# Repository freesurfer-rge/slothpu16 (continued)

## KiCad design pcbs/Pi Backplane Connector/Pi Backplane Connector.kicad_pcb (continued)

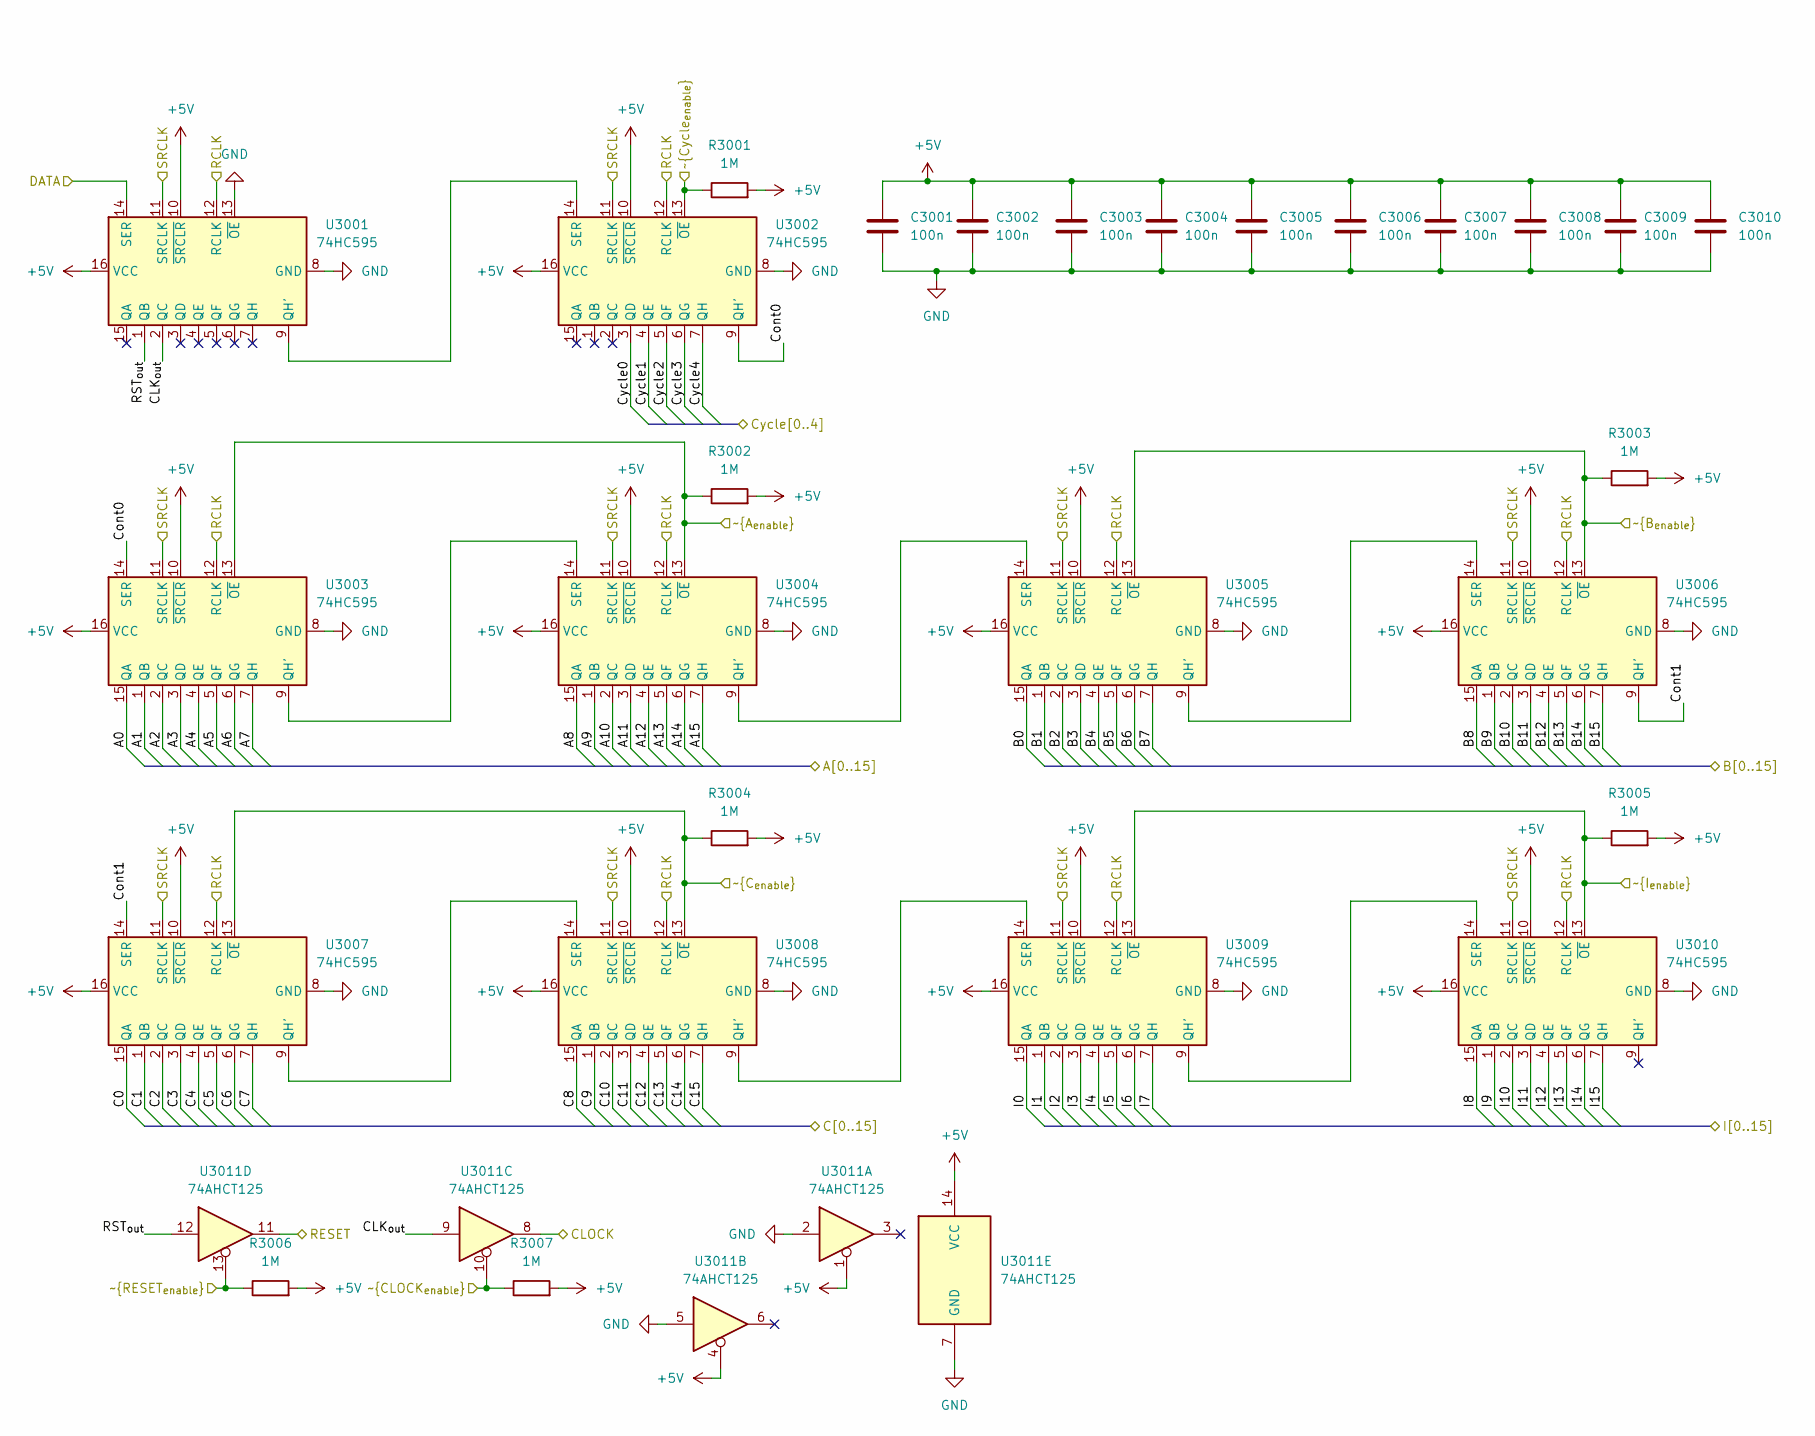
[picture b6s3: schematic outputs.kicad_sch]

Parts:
C3001, C3002, C3003, C3004, C3005, C3006, C3007, C3008, C3009, C3010: 100n; C_0603_1608Metric; LCSC C14663
R3001, R3002, R3003, R3004, R3005, R3006, R3007: 1M; R_0603_1608Metric; LCSC C22935
U3001, U3002, U3003, U3004, U3005, U3006, U3007, U3008, U3009, U3010: 74HC595; SO-16_3.9x9.9mm_P1.27mm; LCSC C5947
U3011: 74AHCT125; DIP-14_W7.62mm_Socket

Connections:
+5V: C3001.2, C3002.2, C3003.2, C3004.2, C3005.2, C3006.2, C3007.2, C3008.2, C3009.2, C3010.2, R3001.2, R3002.2, R3003.2, R3004.2, R3005.2, R3006.2, R3007.2, U3001.10 (~SRCLR), U3001.16 (VCC), U3002.10 (~SRCLR), U3002.16 (VCC), U3003.10 (~SRCLR), U3003.16 (VCC), U3004.10 (~SRCLR), U3004.16 (VCC), U3005.10 (~SRCLR), U3005.16 (VCC), U3006.10 (~SRCLR), U3006.16 (VCC), U3007.10 (~SRCLR), U3007.16 (VCC), U3008.10 (~SRCLR), U3008.16 (VCC), U3009.10 (~SRCLR), U3009.16 (VCC), U3010.10 (~SRCLR), U3010.16 (VCC), U3011.1, U3011.4, U3011.14 (VCC); also elsewhere on the board
/A0: U3003.15 (QA); also elsewhere on the board
/A1: U3003.1 (QB); also elsewhere on the board
/A2: U3003.2 (QC); also elsewhere on the board
/A3: U3003.3 (QD); also elsewhere on the board
/A4: U3003.4 (QE); also elsewhere on the board
/A5: U3003.5 (QF); also elsewhere on the board
/A6: U3003.6 (QG); also elsewhere on the board
/A7: U3003.7 (QH); also elsewhere on the board
/A8: U3004.15 (QA); also elsewhere on the board
/A9: U3004.1 (QB); also elsewhere on the board
/A10: U3004.2 (QC); also elsewhere on the board
/A11: U3004.3 (QD); also elsewhere on the board
/A12: U3004.4 (QE); also elsewhere on the board
/A13: U3004.5 (QF); also elsewhere on the board
/A14: U3004.6 (QG); also elsewhere on the board
/A15: U3004.7 (QH); also elsewhere on the board
/B0: U3005.15 (QA); also elsewhere on the board
/B1: U3005.1 (QB); also elsewhere on the board
/B2: U3005.2 (QC); also elsewhere on the board
/B3: U3005.3 (QD); also elsewhere on the board
/B4: U3005.4 (QE); also elsewhere on the board
/B5: U3005.5 (QF); also elsewhere on the board
/B6: U3005.6 (QG); also elsewhere on the board
/B7: U3005.7 (QH); also elsewhere on the board
/B8: U3006.15 (QA); also elsewhere on the board
/B9: U3006.1 (QB); also elsewhere on the board
/B10: U3006.2 (QC); also elsewhere on the board
/B11: U3006.3 (QD); also elsewhere on the board
/B12: U3006.4 (QE); also elsewhere on the board
/B13: U3006.5 (QF); also elsewhere on the board
/B14: U3006.6 (QG); also elsewhere on the board
/B15: U3006.7 (QH); also elsewhere on the board
/C0: U3007.15 (QA); also elsewhere on the board
/C1: U3007.1 (QB); also elsewhere on the board
/C2: U3007.2 (QC); also elsewhere on the board
/C3: U3007.3 (QD); also elsewhere on the board
/C4: U3007.4 (QE); also elsewhere on the board
/C5: U3007.5 (QF); also elsewhere on the board
/C6: U3007.6 (QG); also elsewhere on the board
/C7: U3007.7 (QH); also elsewhere on the board
/C8: U3008.15 (QA); also elsewhere on the board
/C9: U3008.1 (QB); also elsewhere on the board
/C10: U3008.2 (QC); also elsewhere on the board
/C11: U3008.3 (QD); also elsewhere on the board
/C12: U3008.4 (QE); also elsewhere on the board
/C13: U3008.5 (QF); also elsewhere on the board
/C14: U3008.6 (QG); also elsewhere on the board
/C15: U3008.7 (QH); also elsewhere on the board
/CLOCK: U3011.8; also elsewhere on the board
/Cycle0: U3002.3 (QD); also elsewhere on the board
/Cycle1: U3002.4 (QE); also elsewhere on the board
/Cycle2: U3002.5 (QF); also elsewhere on the board
/Cycle3: U3002.6 (QG); also elsewhere on the board
/Cycle4: U3002.7 (QH); also elsewhere on the board
/I0: U3009.15 (QA); also elsewhere on the board
/I1: U3009.1 (QB); also elsewhere on the board
/I2: U3009.2 (QC); also elsewhere on the board
/I3: U3009.3 (QD); also elsewhere on the board
/I4: U3009.4 (QE); also elsewhere on the board
/I5: U3009.5 (QF); also elsewhere on the board
/I6: U3009.6 (QG); also elsewhere on the board
/I7: U3009.7 (QH); also elsewhere on the board
/I8: U3010.15 (QA); also elsewhere on the board
/I9: U3010.1 (QB); also elsewhere on the board
/I10: U3010.2 (QC); also elsewhere on the board
/I11: U3010.3 (QD); also elsewhere on the board
/I12: U3010.4 (QE); also elsewhere on the board
/I13: U3010.5 (QF); also elsewhere on the board
/I14: U3010.6 (QG); also elsewhere on the board
/I15: U3010.7 (QH); also elsewhere on the board
/Outputs/CLK_{out}: U3001.2 (QC), U3011.9
/Outputs/Cont0: U3002.9 (QH'), U3003.14 (SER)
/Outputs/Cont1: U3006.9 (QH'), U3007.14 (SER)
/Outputs/DATA: U3001.14 (SER); also elsewhere on the board
/Outputs/RCLK: U3001.12 (RCLK), U3002.12 (RCLK), U3003.12 (RCLK), U3004.12 (RCLK), U3005.12 (RCLK), U3006.12 (RCLK), U3007.12 (RCLK), U3008.12 (RCLK), U3009.12 (RCLK), U3010.12 (RCLK); also elsewhere on the board
/Outputs/RST_{out}: U3001.1 (QB), U3011.12
/Outputs/SRCLK: U3001.11 (SRCLK), U3002.11 (SRCLK), U3003.11 (SRCLK), U3004.11 (SRCLK), U3005.11 (SRCLK), U3006.11 (SRCLK), U3007.11 (SRCLK), U3008.11 (SRCLK), U3009.11 (SRCLK), U3010.11 (SRCLK); also elsewhere on the board
/Outputs/~A_{enable}: R3002.1, U3003.13 (~OE), U3004.13 (~OE); also elsewhere on the board
/Outputs/~B_{enable}: R3003.1, U3005.13 (~OE), U3006.13 (~OE); also elsewhere on the board
/Outputs/~CLOCK_{enable}: R3007.1, U3011.10; also elsewhere on the board
/Outputs/~C_{enable}: R3004.1, U3007.13 (~OE), U3008.13 (~OE); also elsewhere on the board
/Outputs/~Cycle_{enable}: R3001.1, U3002.13 (~OE); also elsewhere on the board
/Outputs/~I_{enable}: R3005.1, U3009.13 (~OE), U3010.13 (~OE); also elsewhere on the board
/Outputs/~RESET_{enable}: R3006.1, U3011.13; also elsewhere on the board
/RESET: U3011.11; also elsewhere on the board
GND: C3001.1, C3002.1, C3003.1, C3004.1, C3005.1, C3006.1, C3007.1, C3008.1, C3009.1, C3010.1, U3001.8 (GND), U3001.13 (~OE), U3002.8 (GND), U3003.8 (GND), U3004.8 (GND), U3005.8 (GND), U3006.8 (GND), U3007.8 (GND), U3008.8 (GND), U3009.8 (GND), U3010.8 (GND), U3011.2, U3011.5, U3011.7 (GND); also elsewhere on the board
unnamed: U3001.9 (QH'), U3002.14 (SER)
unnamed: U3003.9 (QH'), U3004.14 (SER)
unnamed: U3004.9 (QH'), U3005.14 (SER)
unnamed: U3005.9 (QH'), U3006.14 (SER)
unnamed: U3007.9 (QH'), U3008.14 (SER)
unnamed: U3008.9 (QH'), U3009.14 (SER)
unnamed: U3009.9 (QH'), U3010.14 (SER)

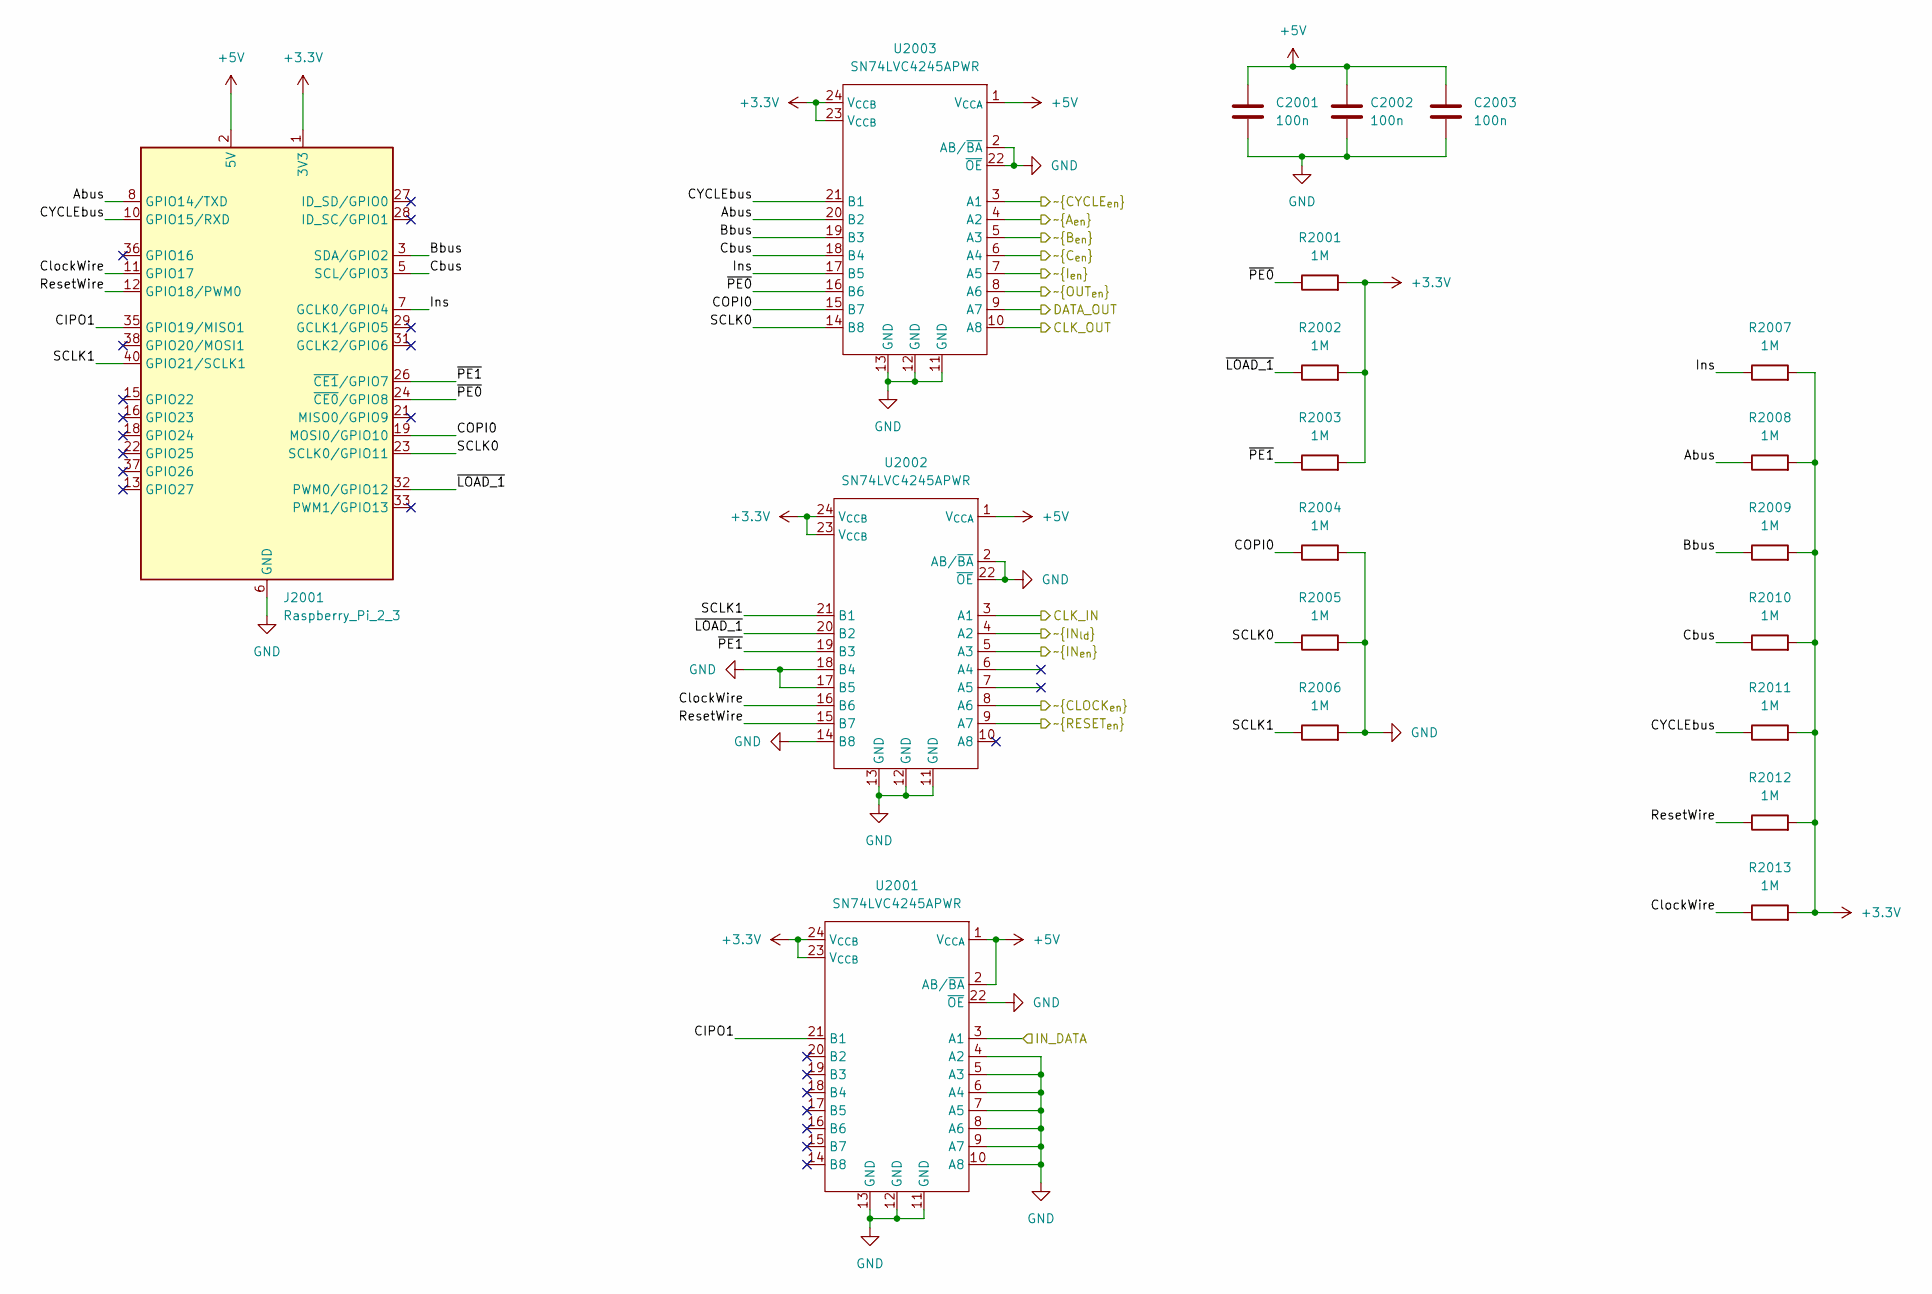
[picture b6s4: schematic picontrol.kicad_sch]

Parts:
C2001, C2002, C2003: 100n; C_0603_1608Metric; LCSC C14663
J2001: Raspberry_Pi_2_3; PinHeader_2x20_P2.54mm_Vertical
R2001, R2002, R2003, R2004, R2005, R2006, R2007, R2008, R2009, R2010, R2011, R2012, R2013: 1M; R_0603_1608Metric; LCSC C22935
U2001, U2002, U2003: SN74LVC4245APWR; TSSOP-24_4.4x7.8mm_P0.65mm; LCSC C7859

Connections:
+3.3V: J2001.1 (3V3), J2001.17 (3V3), R2001.2, R2002.2, R2003.2, R2007.2, R2008.2, R2009.2, R2010.2, R2011.2, R2012.2, R2013.2, U2001.23 (V_{CCB}), U2001.24 (V_{CCB}), U2002.23 (V_{CCB}), U2002.24 (V_{CCB}), U2003.23 (V_{CCB}), U2003.24 (V_{CCB})
+5V: C2001.2, C2002.2, C2003.2, J2001.2 (5V), J2001.4 (5V), U2001.1 (V_{CCA}), U2001.2 (AB/~BA), U2002.1 (V_{CCA}), U2003.1 (V_{CCA}); also elsewhere on the board
/Inputs/IN_{CLK}: U2002.3 (A1); also elsewhere on the board
/Inputs/IN_{DATA}: U2001.3 (A1); also elsewhere on the board
/Inputs/~IN_{LOAD}: U2002.4 (A2); also elsewhere on the board
/Inputs/~IN_{SELECT}: U2002.5 (A3); also elsewhere on the board
/Outputs/DATA: U2003.9 (A7); also elsewhere on the board
/Outputs/RCLK: U2003.8 (A6); also elsewhere on the board
/Outputs/SRCLK: U2003.10 (A8); also elsewhere on the board
/Outputs/~A_{enable}: U2003.4 (A2); also elsewhere on the board
/Outputs/~B_{enable}: U2003.5 (A3); also elsewhere on the board
/Outputs/~CLOCK_{enable}: U2002.8 (A6); also elsewhere on the board
/Outputs/~C_{enable}: U2003.6 (A4); also elsewhere on the board
/Outputs/~Cycle_{enable}: U2003.3 (A1); also elsewhere on the board
/Outputs/~I_{enable}: U2003.7 (A5); also elsewhere on the board
/Outputs/~RESET_{enable}: U2002.9 (A7); also elsewhere on the board
/Pi Control/Abus: J2001.8 (GPIO14/TXD), R2008.1, U2003.20 (B2)
/Pi Control/Bbus: J2001.3 (SDA/GPIO2), R2009.1, U2003.19 (B3)
/Pi Control/CIPO1: J2001.35 (GPIO19/MISO1), U2001.21 (B1)
/Pi Control/COPI0: J2001.19 (MOSI0/GPIO10), R2004.1, U2003.15 (B7)
/Pi Control/CYCLEbus: J2001.10 (GPIO15/RXD), R2011.1, U2003.21 (B1)
/Pi Control/Cbus: J2001.5 (SCL/GPIO3), R2010.1, U2003.18 (B4)
/Pi Control/ClockWire: J2001.11 (GPIO17), R2013.1, U2002.16 (B6)
/Pi Control/Ins: J2001.7 (GCLK0/GPIO4), R2007.1, U2003.17 (B5)
/Pi Control/ResetWire: J2001.12 (GPIO18/PWM0), R2012.1, U2002.15 (B7)
/Pi Control/SCLK0: J2001.23 (SCLK0/GPIO11), R2005.1, U2003.14 (B8)
/Pi Control/SCLK1: J2001.40 (GPIO21/SCLK1), R2006.1, U2002.21 (B1)
/Pi Control/~LOAD_1: J2001.32 (PWM0/GPIO12), R2002.1, U2002.20 (B2)
/Pi Control/~PE0: J2001.24 (~CE0/GPIO8), R2001.1, U2003.16 (B6)
/Pi Control/~PE1: J2001.26 (~CE1/GPIO7), R2003.1, U2002.19 (B3)
GND: C2001.1, C2002.1, C2003.1, J2001.6 (GND), J2001.9 (GND), J2001.14 (GND), J2001.20 (GND), J2001.25 (GND), J2001.30 (GND), J2001.34 (GND), J2001.39 (GND), R2004.2, R2005.2, R2006.2, U2001.4 (A2), U2001.5 (A3), U2001.6 (A4), U2001.7 (A5), U2001.8 (A6), U2001.9 (A7), U2001.10 (A8), U2001.11 (GND), U2001.12 (GND), U2001.13 (GND), U2001.22 (~OE), U2002.2 (AB/~BA), U2002.11 (GND), U2002.12 (GND), U2002.13 (GND), U2002.14 (B8), U2002.17 (B5), U2002.18 (B4), U2002.22 (~OE), U2003.2 (AB/~BA), U2003.11 (GND), U2003.12 (GND), U2003.13 (GND), U2003.22 (~OE); also elsewhere on the board

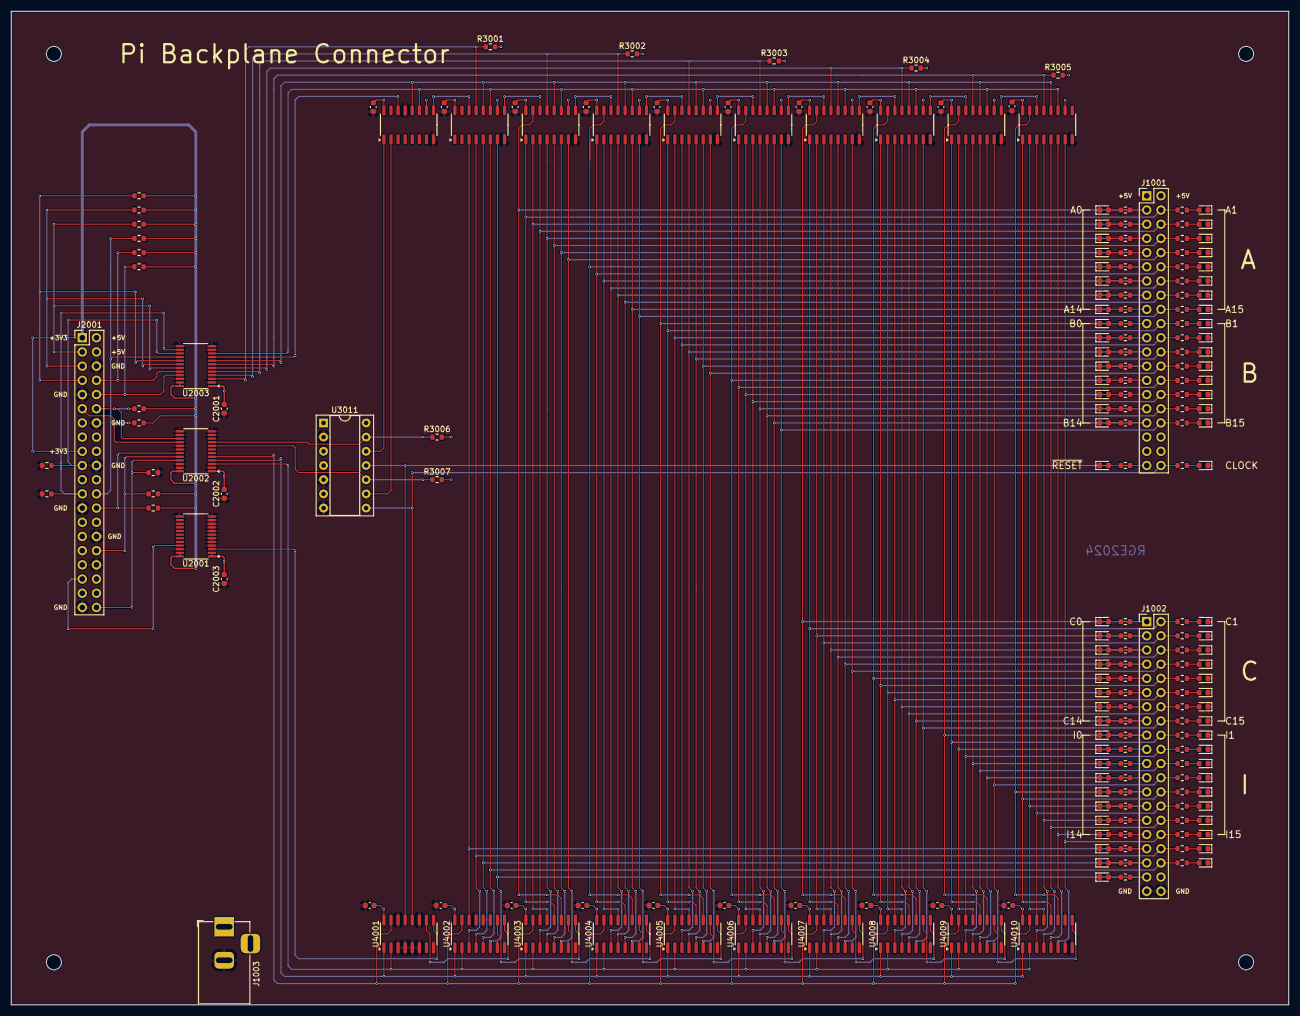
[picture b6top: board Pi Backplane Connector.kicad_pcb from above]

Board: 2 copper layers, 228.6 x 177.8 mm, 217 parts (0 on the bottom side), 193 nets.

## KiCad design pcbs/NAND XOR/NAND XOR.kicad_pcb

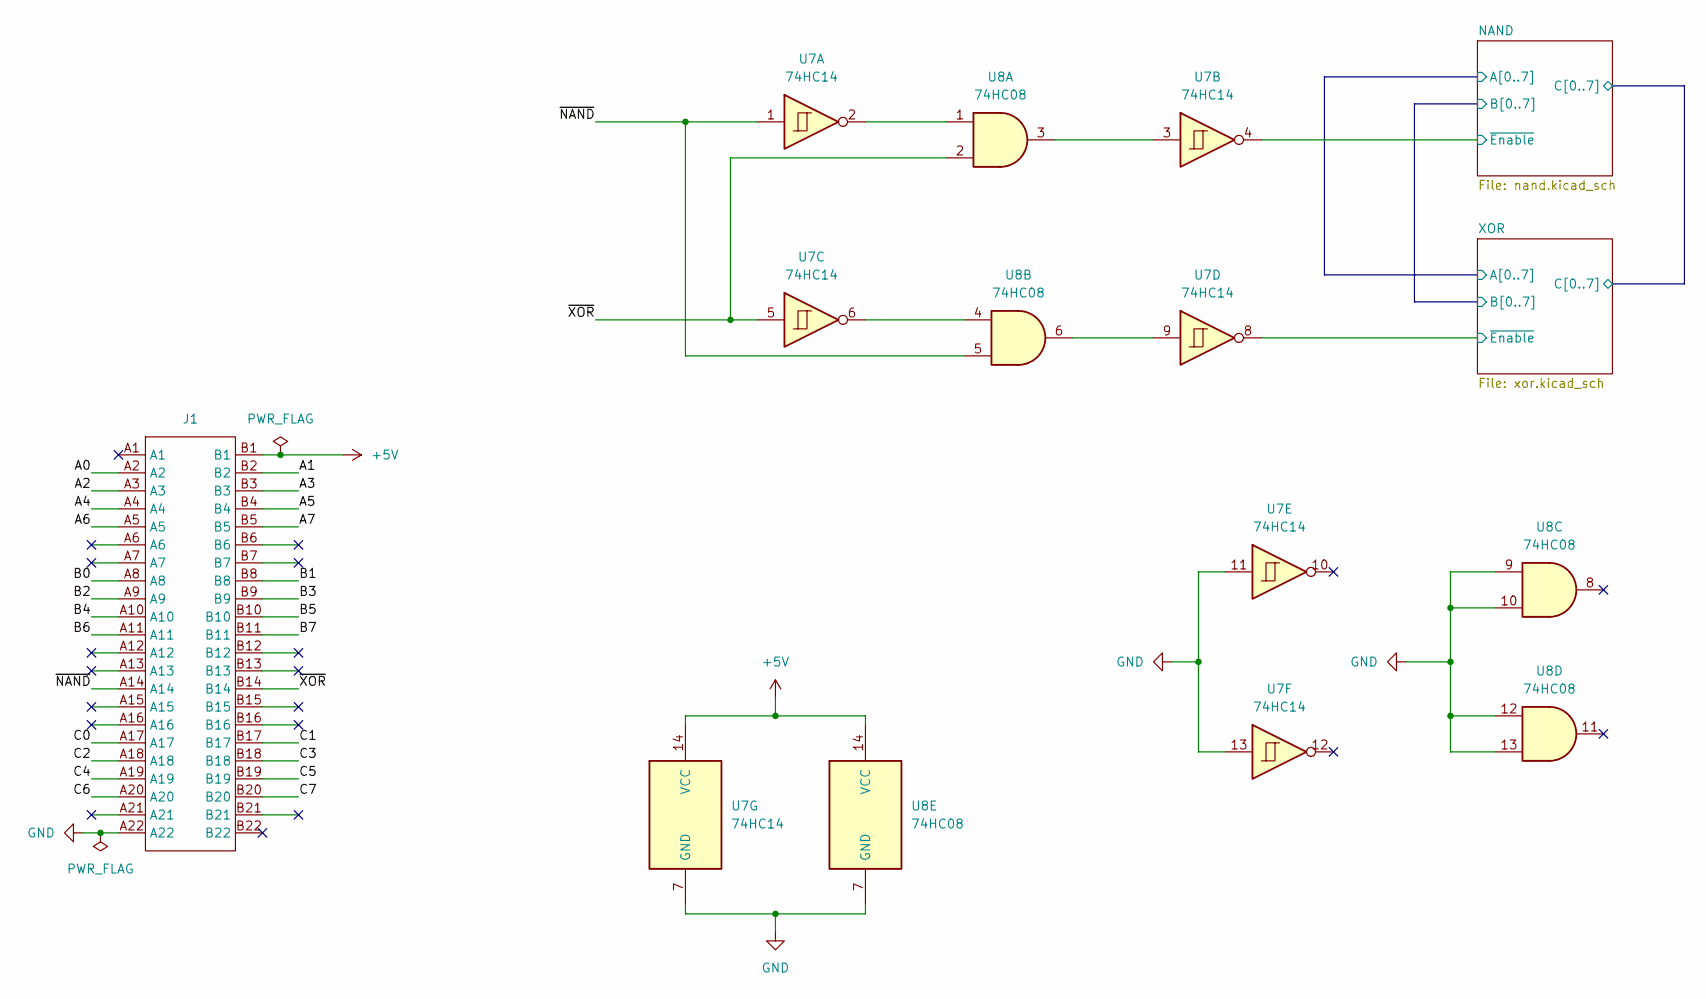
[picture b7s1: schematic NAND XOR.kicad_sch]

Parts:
J1: TE-5530843-4-Edge
U7: 74HC14; SOIC-14_3.9x8.7mm_P1.27mm; LCSC C5605
U8: 74HC08; SOIC-14_3.9x8.7mm_P1.27mm; LCSC C5593

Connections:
+5V: J1.B1, U7.14 (VCC), U8.14 (VCC); also elsewhere on the board
/NAND/A0: J1.A2; also elsewhere on the board
/NAND/A1: J1.B2; also elsewhere on the board
/NAND/A2: J1.A3; also elsewhere on the board
/NAND/A3: J1.B3; also elsewhere on the board
/NAND/A4: J1.A4; also elsewhere on the board
/NAND/A5: J1.B4; also elsewhere on the board
/NAND/A6: J1.A5; also elsewhere on the board
/NAND/A7: J1.B5; also elsewhere on the board
/NAND/B0: J1.A8; also elsewhere on the board
/NAND/B1: J1.B8; also elsewhere on the board
/NAND/B2: J1.A9; also elsewhere on the board
/NAND/B3: J1.B9; also elsewhere on the board
/NAND/B4: J1.A10; also elsewhere on the board
/NAND/B5: J1.B10; also elsewhere on the board
/NAND/B6: J1.A11; also elsewhere on the board
/NAND/B7: J1.B11; also elsewhere on the board
/NAND/C0: J1.A17; also elsewhere on the board
/NAND/C1: J1.B17; also elsewhere on the board
/NAND/C2: J1.A18; also elsewhere on the board
/NAND/C3: J1.B18; also elsewhere on the board
/NAND/C4: J1.A19; also elsewhere on the board
/NAND/C5: J1.B19; also elsewhere on the board
/NAND/C6: J1.A20; also elsewhere on the board
/NAND/C7: J1.B20; also elsewhere on the board
/NAND/~Enable: U7.4; also elsewhere on the board
/XOR/~Enable: U7.8; also elsewhere on the board
/~NAND: J1.A14, U7.1, U8.5
/~XOR: J1.B14, U7.5, U8.2
GND: J1.A22, U7.7 (GND), U7.11, U7.13, U8.7 (GND), U8.9, U8.10, U8.12, U8.13; also elsewhere on the board
unnamed: U7.2, U8.1
unnamed: U7.3, U8.3
unnamed: U7.6, U8.4
unnamed: U7.9, U8.6

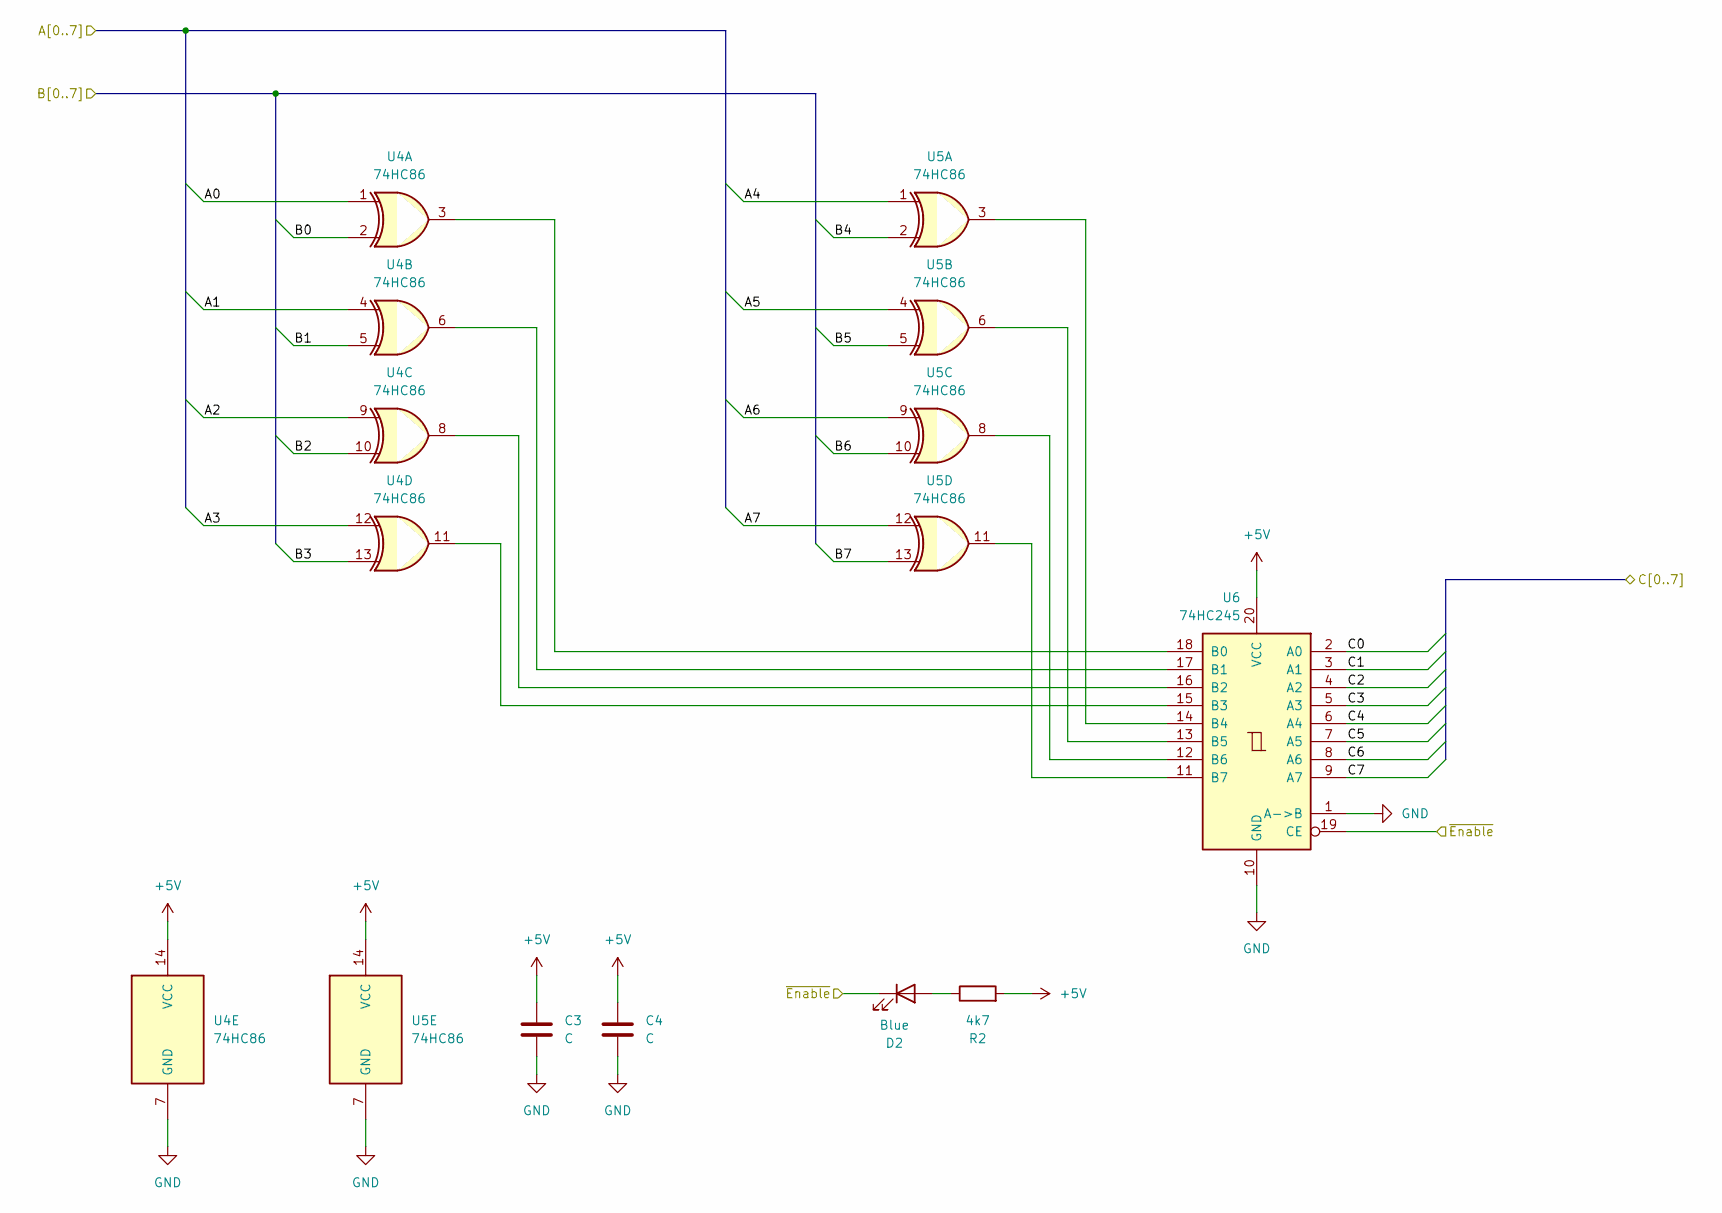
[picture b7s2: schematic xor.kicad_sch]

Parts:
C3, C4: C; C_0603_1608Metric; LCSC C14663
D2: Blue; LED_0603_1608Metric; LCSC C72041
R2: 4k7; R_0603_1608Metric; LCSC C23162
U4, U5: 74HC86; DIP-14_W7.62mm_Socket
U6: 74HC245; SOIC-20W_7.5x12.8mm_P1.27mm; LCSC C5625

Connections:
+5V: C3.1, C4.1, R2.2, U4.14 (VCC), U5.14 (VCC), U6.20 (VCC); also elsewhere on the board
/NAND/A0: U4.1; also elsewhere on the board
/NAND/A1: U4.4; also elsewhere on the board
/NAND/A2: U4.9; also elsewhere on the board
/NAND/A3: U4.12; also elsewhere on the board
/NAND/A4: U5.1; also elsewhere on the board
/NAND/A5: U5.4; also elsewhere on the board
/NAND/A6: U5.9; also elsewhere on the board
/NAND/A7: U5.12; also elsewhere on the board
/NAND/B0: U4.2; also elsewhere on the board
/NAND/B1: U4.5; also elsewhere on the board
/NAND/B2: U4.10; also elsewhere on the board
/NAND/B3: U4.13; also elsewhere on the board
/NAND/B4: U5.2; also elsewhere on the board
/NAND/B5: U5.5; also elsewhere on the board
/NAND/B6: U5.10; also elsewhere on the board
/NAND/B7: U5.13; also elsewhere on the board
/NAND/C0: U6.2 (A0); also elsewhere on the board
/NAND/C1: U6.3 (A1); also elsewhere on the board
/NAND/C2: U6.4 (A2); also elsewhere on the board
/NAND/C3: U6.5 (A3); also elsewhere on the board
/NAND/C4: U6.6 (A4); also elsewhere on the board
/NAND/C5: U6.7 (A5); also elsewhere on the board
/NAND/C6: U6.8 (A6); also elsewhere on the board
/NAND/C7: U6.9 (A7); also elsewhere on the board
/XOR/~Enable: D2.1 (K), U6.19 (CE); also elsewhere on the board
GND: C3.2, C4.2, U4.7 (GND), U5.7 (GND), U6.1 (A->B), U6.10 (GND); also elsewhere on the board
unnamed: D2.2 (A), R2.1
unnamed: U4.3, U6.18 (B0)
unnamed: U4.6, U6.17 (B1)
unnamed: U4.8, U6.16 (B2)
unnamed: U4.11, U6.15 (B3)
unnamed: U5.3, U6.14 (B4)
unnamed: U5.6, U6.13 (B5)
unnamed: U5.8, U6.12 (B6)
unnamed: U5.11, U6.11 (B7)

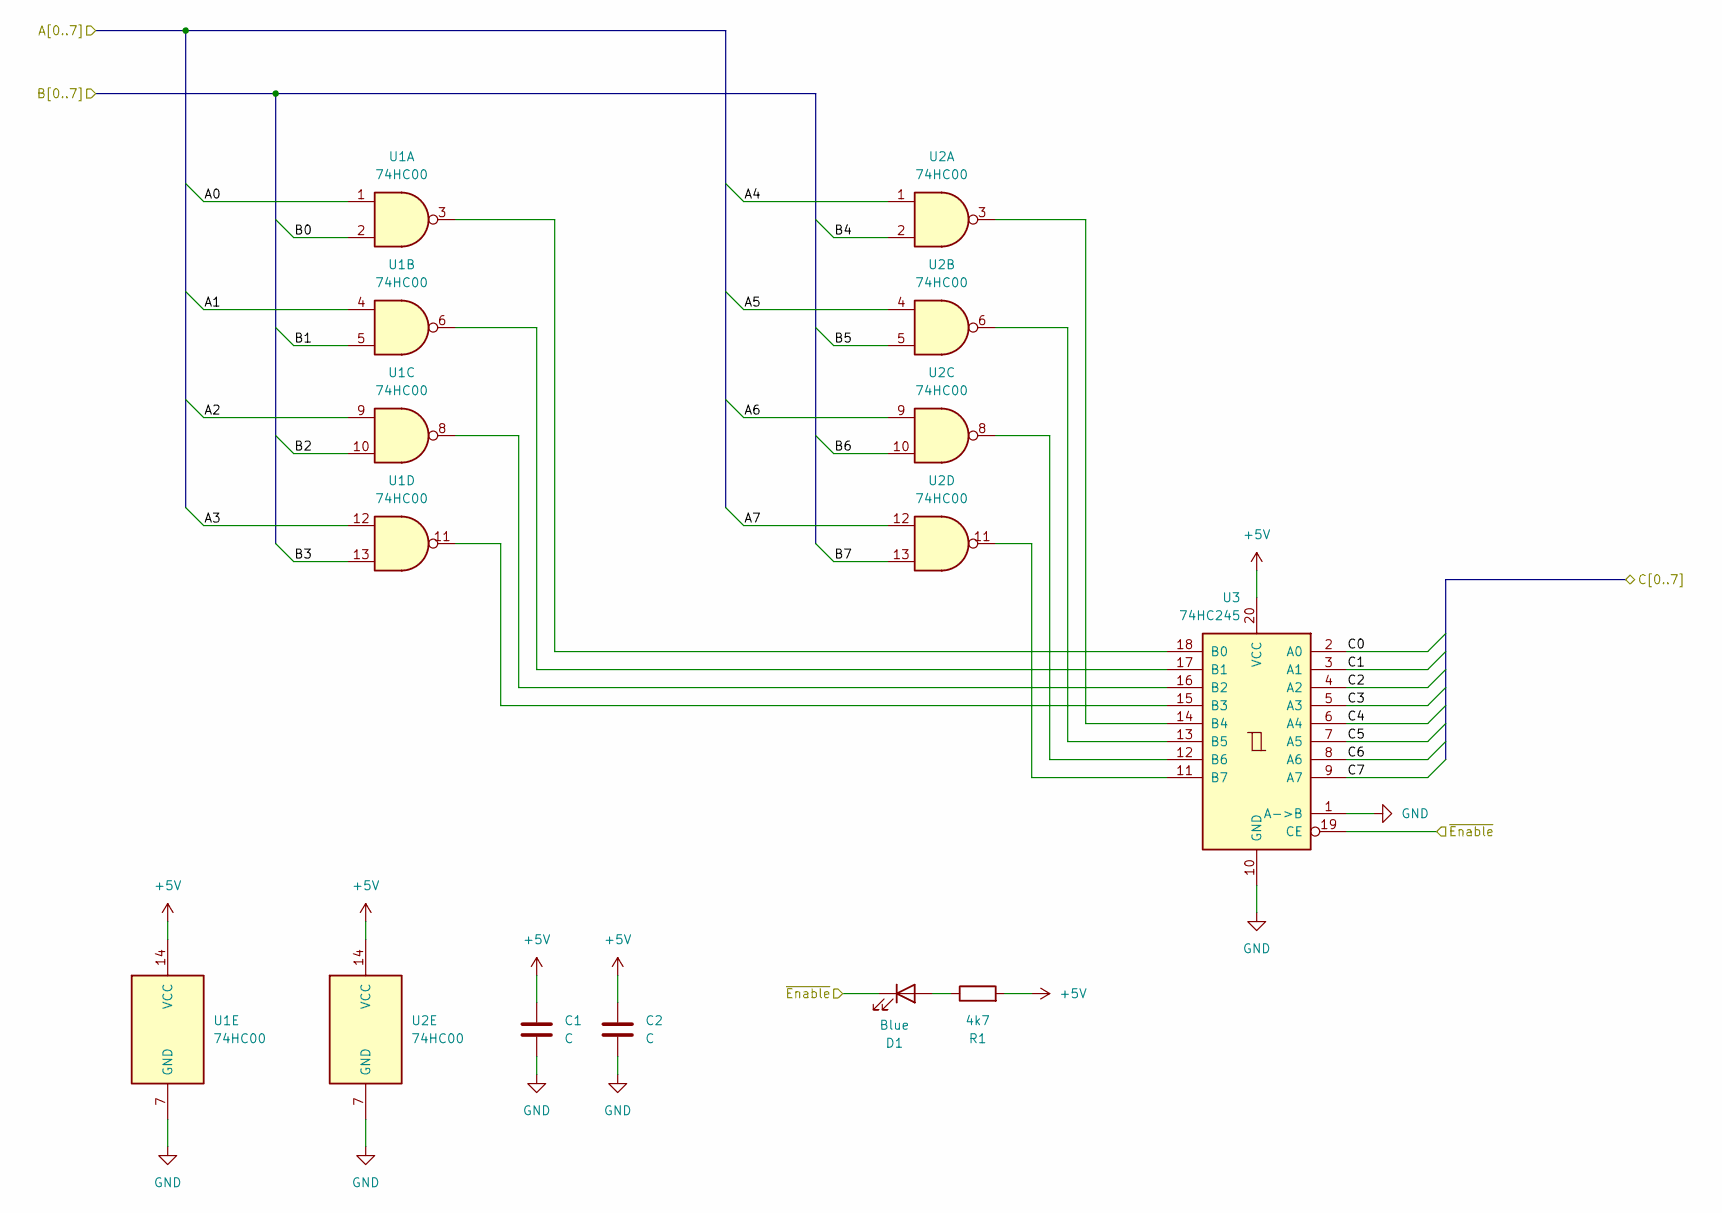
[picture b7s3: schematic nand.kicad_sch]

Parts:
C1, C2: C; C_0603_1608Metric; LCSC C14663
D1: Blue; LED_0603_1608Metric; LCSC C72041
R1: 4k7; R_0603_1608Metric; LCSC C23162
U1, U2: 74HC00; DIP-14_W7.62mm_Socket
U3: 74HC245; SOIC-20W_7.5x12.8mm_P1.27mm; LCSC C5625

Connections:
+5V: C1.1, C2.1, R1.2, U1.14 (VCC), U2.14 (VCC), U3.20 (VCC); also elsewhere on the board
/NAND/A0: U1.1; also elsewhere on the board
/NAND/A1: U1.4; also elsewhere on the board
/NAND/A2: U1.9; also elsewhere on the board
/NAND/A3: U1.12; also elsewhere on the board
/NAND/A4: U2.1; also elsewhere on the board
/NAND/A5: U2.4; also elsewhere on the board
/NAND/A6: U2.9; also elsewhere on the board
/NAND/A7: U2.12; also elsewhere on the board
/NAND/B0: U1.2; also elsewhere on the board
/NAND/B1: U1.5; also elsewhere on the board
/NAND/B2: U1.10; also elsewhere on the board
/NAND/B3: U1.13; also elsewhere on the board
/NAND/B4: U2.2; also elsewhere on the board
/NAND/B5: U2.5; also elsewhere on the board
/NAND/B6: U2.10; also elsewhere on the board
/NAND/B7: U2.13; also elsewhere on the board
/NAND/C0: U3.2 (A0); also elsewhere on the board
/NAND/C1: U3.3 (A1); also elsewhere on the board
/NAND/C2: U3.4 (A2); also elsewhere on the board
/NAND/C3: U3.5 (A3); also elsewhere on the board
/NAND/C4: U3.6 (A4); also elsewhere on the board
/NAND/C5: U3.7 (A5); also elsewhere on the board
/NAND/C6: U3.8 (A6); also elsewhere on the board
/NAND/C7: U3.9 (A7); also elsewhere on the board
/NAND/~Enable: D1.1 (K), U3.19 (CE); also elsewhere on the board
GND: C1.2, C2.2, U1.7 (GND), U2.7 (GND), U3.1 (A->B), U3.10 (GND); also elsewhere on the board
unnamed: D1.2 (A), R1.1
unnamed: U1.3, U3.18 (B0)
unnamed: U1.6, U3.17 (B1)
unnamed: U1.8, U3.16 (B2)
unnamed: U1.11, U3.15 (B3)
unnamed: U2.3, U3.14 (B4)
unnamed: U2.6, U3.13 (B5)
unnamed: U2.8, U3.12 (B6)
unnamed: U2.11, U3.11 (B7)

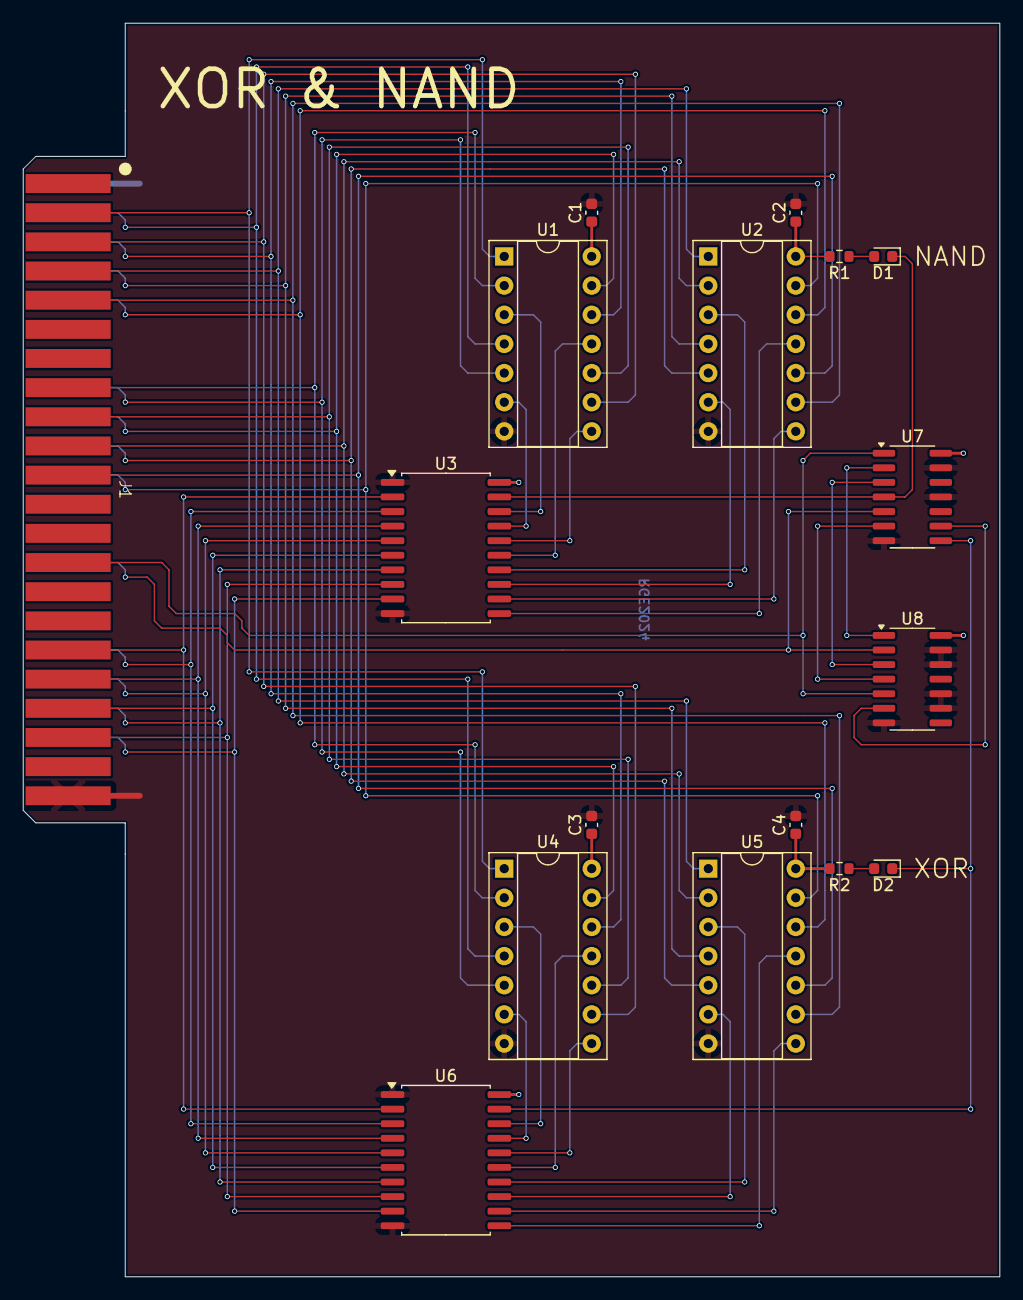
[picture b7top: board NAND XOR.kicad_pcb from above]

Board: 2 copper layers, 85.1 x 109.2 mm, 17 parts (0 on the bottom side), 52 nets.
